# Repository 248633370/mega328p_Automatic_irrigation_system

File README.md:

# mega328p_Automatic_irrigation_system
Yet another automatic irrigation system

System based on atmega328p (Arduino can be used - overkill, but was designed for "on hands" materials).
It measure humidity about each 12 hours by two-needle sensor.

Device powered from ATX PSU +5V standby, and manage PS_ON by optocoupler for start PSU and use +12V through relay for drive water pump.
Device irrigate 10 seconds(hardcoded), after that measure humidity one more time to determine need iriigate once more.

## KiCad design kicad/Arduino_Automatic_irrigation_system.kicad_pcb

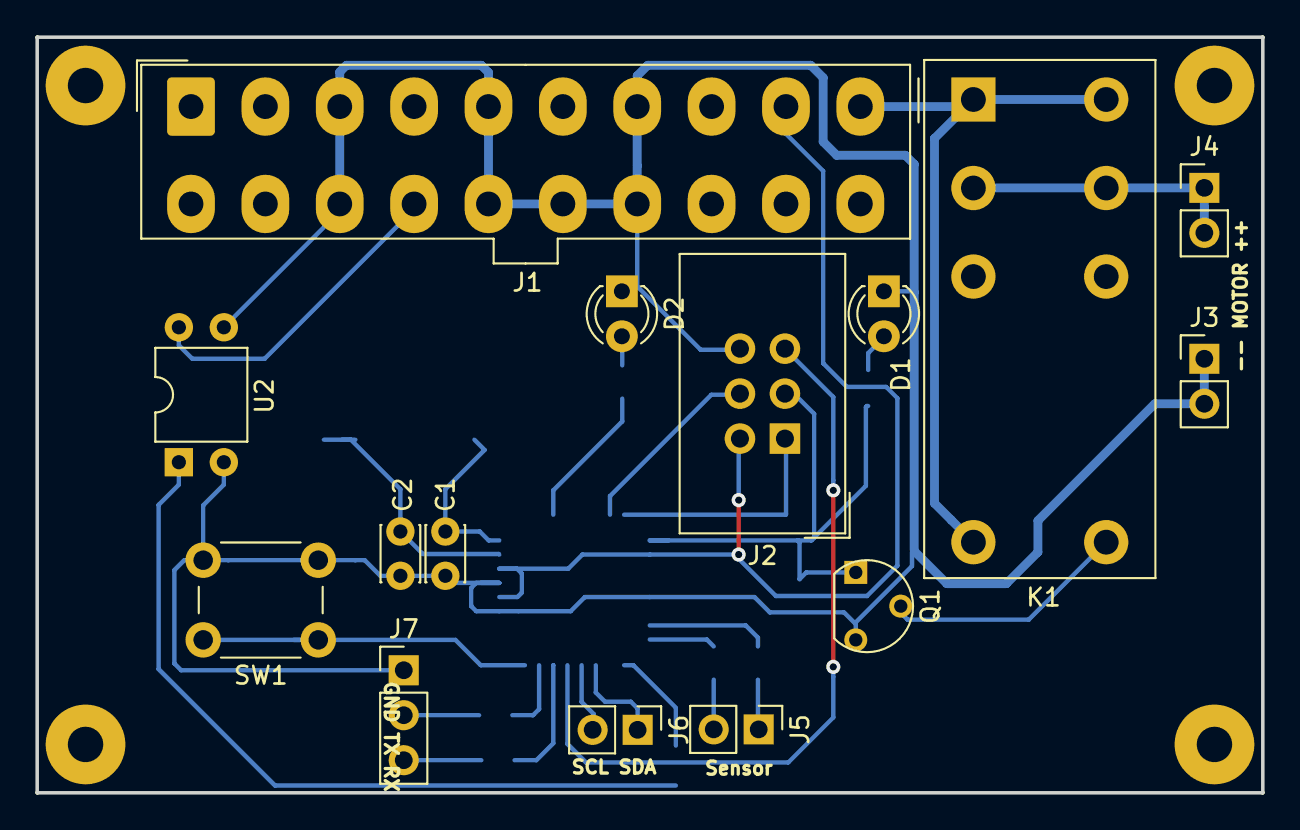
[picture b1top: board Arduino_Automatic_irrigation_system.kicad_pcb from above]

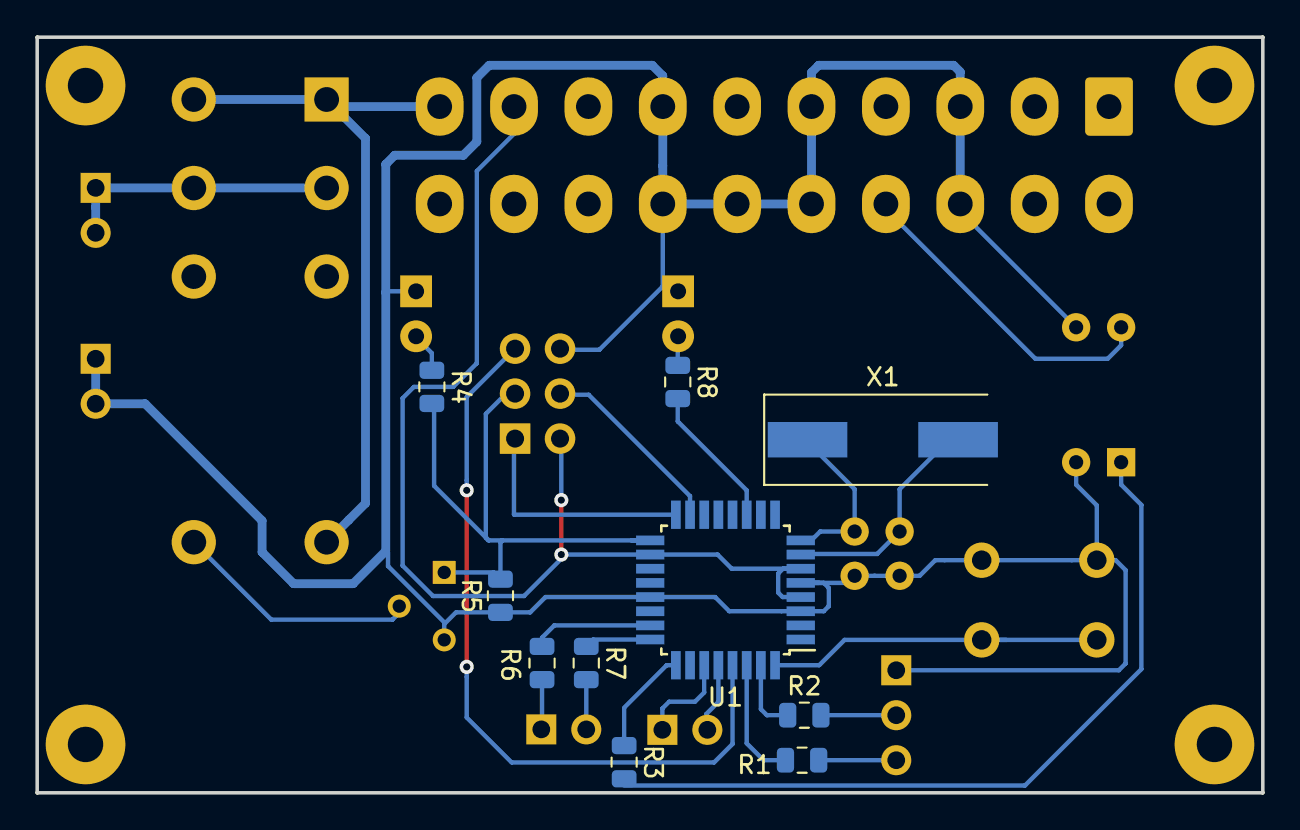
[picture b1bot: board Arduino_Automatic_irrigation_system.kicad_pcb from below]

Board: 2 copper layers, 69.2 x 42.7 mm, 25 parts (10 on the bottom side), 28 nets.

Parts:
C1, C2: 22p; C_Disc_D3.0mm_W2.0mm_P2.50mm
D1, D2: LED; LED_D3.0mm
J1: Conn_02x10_Top_Bottom; Molex_Mini-Fit_Jr_5566-20A_2x10_P4.20mm_Vertical
J2: AVR-ISP-6; IDC-Header_2x03_P2.54mm_Vertical
J3: Motor-; PinHeader_1x02_P2.54mm_Vertical
J4: Motor+; PinHeader_1x02_P2.54mm_Vertical
J5: Sensor; PinHeader_1x02_P2.54mm_Vertical
J6: sclI2Csda; PinHeader_1x02_P2.54mm_Vertical
J7: GND TX RX; PinHeader_1x03_P2.54mm_Vertical
K1: Fujitsu_FTR-F1C; Relay_DPDT_Fujitsu_FTR-F1C
Q1: BSS295; TO-92_wider_pitch
R1, R2, R4, R8: 1k; R_0805_2012Metric
R3: 100; R_0805_2012Metric
R5, R6, R7: 100k; R_0805_2012Metric
SW1: SW_Push; SW_PUSH_6mm_H9.5mm
U1: ATmega328P-AU; TQFP-32_7x7mm_P0.8mm
U2: SFH617A-4; DIP-4_W7.62mm
X1: 16MHz; Crystal_SMD_HC49-SD

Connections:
+5V: J1.9, J2.2, U1.4, U1.6, U1.18
+12V: J1.10, K1.1, K1.4, K1.8
ADC0: R6.1, U1.23
ADC1: R7.1, U1.24
GND: C1.2, C2.2, D1.1, D2.1, J1.3, J1.5, J1.7, J1.13, J1.15, J1.16, J1.17, J2.6, J3.1, J3.2, J7.1, Q1.3, R5.1, SW1.2, U1.3, U1.5, U1.21, U2.2, U2.3
MISO: J2.1, U1.16
MOSI: J2.4, U1.15
unnamed: C1.1, U1.8, X1.1
unnamed: C2.1, U1.7, X1.2
unnamed: D1.2, R4.1
unnamed: D2.2, R8.1
unnamed: J1.14, U2.4
unnamed: J4.1, J4.2, K1.2, K1.7
unnamed: J5.1, R6.2
unnamed: J5.2, R7.2
unnamed: K1.5, Q1.2
unnamed: R1.1, U1.30
unnamed: R2.1, U1.31
unnamed: R3.1, U1.25
unnamed: R3.2, U2.1
unnamed: R8.2, U1.11
unnamed: SW1.1, U1.32
RST: J2.5, U1.29
RX: J7.3, R1.2
SCK: J2.3, Q1.1, R4.2, R5.2, U1.17
SCL: J6.2, U1.28
SDA: J6.1, U1.27
TX: J7.2, R2.2

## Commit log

2018-09-25 Irrigateion system wit UART and i2c debug
2018-10-29 Heartbeat, UART, i2c
2018-10-29 Working. UART and heartbeat
2018-10-29 CURE "implicit declaration of function itoa"
2018-11-02 Fix typo
2018-11-02 kicad project
